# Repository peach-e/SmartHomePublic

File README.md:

# SmartHome System
Run your home from a Raspberry Pi! Specifically your gardening system and your ambient lights.

## Raspberry Pi Setup
### Notes
* The following steps are written for a Raspberry Pi 2 with a TP-Link Wifi Adapter (RTL8188EUS).
* My LAN router has been configured to recognise the MAC address of the Wi-Fi Adapter and associate it with the `__HOSTNAME_SERVER__` hostname and a fixed IP address.

### Steps
1. Download Raspbian Buster Lite and image it onto an SD Card.
2. Boot Up the Raspberry Pi. Log in with `pi`/`raspberry`.
3. Configure the RPi with `$ sudo raspi-config`:
    * Hostname:
        * Set to something memorable.
    * Password
        * Set to something else that isn't 'raspberry'.
    * Localization Options
        * Timezone: Set
        * Keyboard Layout: US, if you can figure out how to set it.
    * Network Options
        * Hostname: YOUR_HOSTNAME_GOES_HERE
    * Interfacing Options
        * SSH Server: Enable
4. Set Up RPi Wi-Fi to talk to my network.
    * Create a file called `/etc/network/interfaces.d/tplink` with the following lines:
        ```
        auto wlan0
        allow-hotplug wlan0
        iface wlan0 inet manual
        wpa-conf /etc/wpa_supplicant/wpa_supplicant.conf
        ```
    * Edit the file `/etc/wpa_supplicant/wpa_supplicant.conf` so that it reads as follows:
        ```
        ctrl_interface=DIR=/var/run/wpa_supplicant GROUP=netdev
        update_config=1
        country=US

        network={
            scan_ssid=1
            ssid="__WIFI_NETWORK_NAME__"
            psk="__WIFI_NETWORK_PASSWORD__"
        }
        ```
    * Reboot.
5. Install git with `$ sudo apt install git`.
6. Install the RF24 Module as described in the 'RF24 Setup' section.
7. Execute the 'Common Setup Steps'.
8. After running the setup script for the SmartHome project, have a look at the `dist.pth` file nested
   in the `virtualenv` directory and just sanity check that the files listed in there actually exist. If they don't, your RF24 libraries won't work unless you fix this:
    * look around in `/usr/local/lib/` for something related to `RF24<something something>.egg`.
    * update the `dist.pth` file and the setup script to point to the right library locations.
9. Power off the system. Connect any peripherals as required, and start the Pi.
10. Enable any mocks you will need, and practise running the server as root with
    ```
    /home/pi/SmartHome/scripts/start_system_in_background.sh
    ```
    Ensure that you can access the server and things work as expected.
11. If the Pi is intended for production use, modify your `/etc/rc.local` file by adding the following line before
   the exit command. This will enable the server and worker automatically on startup.
    ```
    /home/pi/SmartHome/scripts/start_system_in_background.sh
    ```
   (Double check that the path is correct, depending on where you cloned the repo).

## PC Setup
To get this going on your laptop, all you have to do is run the Common Setup steps. There may be an issue where 
you don't have the RPi python library installed. So just modify the `main.conf` file to enable the mockout. It's
also recommended that you have a solid IDE like Sublime Text ready to go to make some tidy code edits.

## Common Setup
### Dependencies
* Python 3.6+
* Pip3 (via the python3-pip package)
    * If you run `$ pip3 --version` you should see 3-point-something.

### Steps
1. Clone the repository.
    ```
    $ cd ~/Development
    $ git clone ssh://git@__HOSTNAME_LOCAL_GIT_SERVER__/home/git/SmartHome.git
    ```
2. Ensure your Python versions and PIP versions are set up.
3. Run the setup script
    ```
    $ ./scripts/setup_dev_environment.sh
    ```

## RF24 Setup
These steps are based on the Detailed Tutorial on Confluence "Tutorial - RPi + Arduino Hello World", which
were modified from the original steps at http://tmrh20.github.io/RF24/Python.html.

1. On the Raspberry Pi, enable SPI through `raspi-config`. Reboot.
2. Update your software (this might take a while)
    ```
    $ sudo apt update
    $ sudo apt upgrade
    ```
3. Install requisite software.
    ```
    $ sudo apt install python3-dev libboost-python-dev
    ```
4. Get the driver software on your Raspberry Pi.
    ```
    $ git clone https://github.com/nRF24/RF24.git
    ```
5. Change into the driver directory, build, and install the driver.
    ```
    $ cd RF24
    $ make
    $ sudo make install
6. Change into the pyRF24 library, install the setup tools dependency, and build the Python wrapper.
    ```
    $ cd pyRF24
    $ sudo apt install python3-setuptools
    $ python3 setup.py build
    $ sudo python3 setup.py install
    ```

## Normal Development
For use in a non-production environment. Before beginning, enable any mockouts in the `main.conf`
file if you think you need them.
1. After logging in, source the initialization script.
    ```
    $ source init_environment.sh
    ```
2. Change directory into the `app` directory and run the system.
    ```
    $ cd app
    $ ./run_system.py
    ```
Exit the application with Ctrl-C or run `$ killall python`.

## Re-Deployment
1. Deactivate any running systems with
    ```
    # killall python
    # killall python3
    # deactivate
    ```
2. Pull from master.
    ```
    $ git pull origin master
    ```
3. Run a git clean.
    ```
    $ git clean -dxf
    ```
4. Re-Deploy the repo.
    ```
    $ cd scripts
    $ ./setup_dev_environment.sh
    ```
5. Ideally, your default config file will already be set up for a production
   system. But, if you require a non-standard configuration, copy over another main.conf from the template
   and make any changes as necessary.
6. Reboot. Your changes should work.

## Hot Fix to Database
1. Deactivate any running systems with
    ```
    # killall python
    # killall python3
    # deactivate
    ```
2. Pull from master.
    ```
    $ git pull origin master
    ```
3. Update database by modifying `scripts/re_initialize_database.py`.
4. Delete the existing database
    ```
    $ rm db/system.db
    ```
5. Re-Deploy Database.
    ```
    $ . init_environment.sh
    $ ./scripts/re_initialize_database.py
    ```
6. Deactivate environment with `deactivate` and then start the system.
    ```
    $ sudo ./scripts/start_system_in_background.sh
    ```
7. Log out. Server should continue running.

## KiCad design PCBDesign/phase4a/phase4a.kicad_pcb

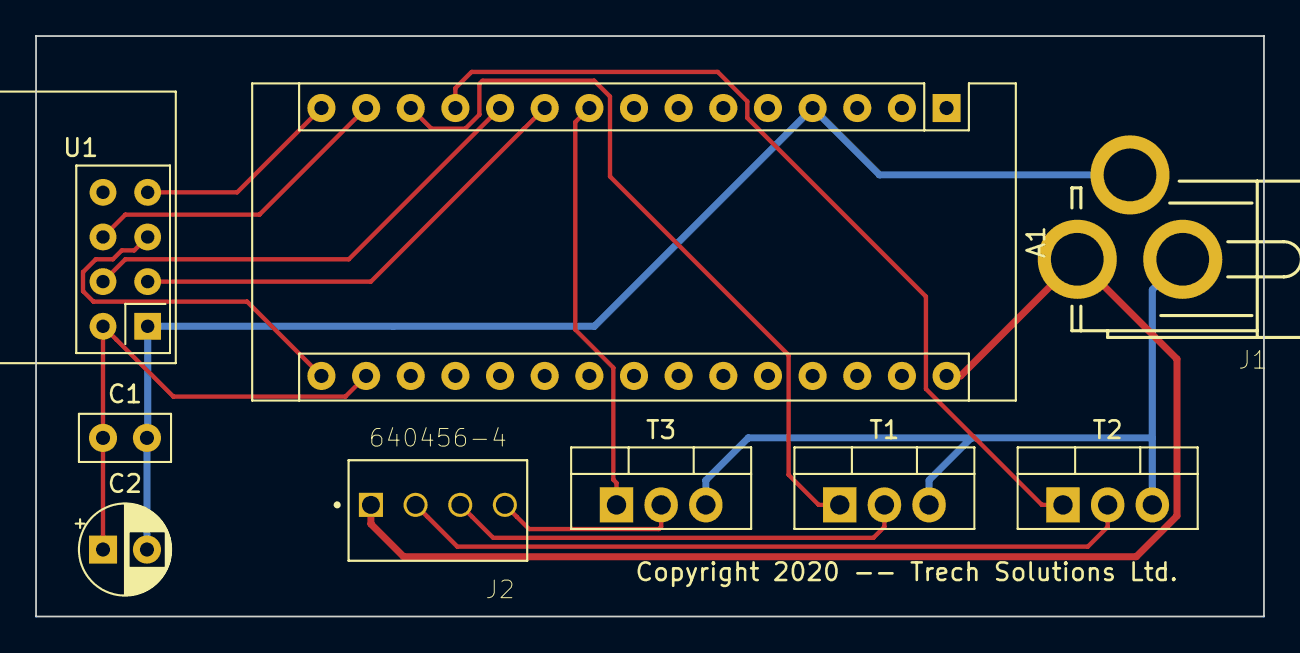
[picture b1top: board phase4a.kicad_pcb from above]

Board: 2 copper layers, 69.9 x 33.0 mm, 9 parts (0 on the bottom side), 14 nets.

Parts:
A1: Arduino_Nano_v2.x; Arduino_Nano
C1: 0.1u; C_Disc_D5.0mm_W2.5mm_P2.50mm
C2: 10u; CP_Radial_D5.0mm_P2.50mm
J1: PJ-002A
J2: 640456-4; TE_640456-4
T1, T2, T3: IRL2703PBF; TO-220-3_Vertical
U1: NRF24L01_Breakout; nRF24L01_Breakout

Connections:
/ARD_B: A1.9, T3.1
/ARD_CE: A1.10, U1.3
/ARD_CSN: A1.11, U1.4
/ARD_G: A1.12, T2.1
/ARD_MISO: A1.15, U1.7
/ARD_MOSI: A1.14, U1.6
/ARD_R: A1.13, T1.1
/ARD_RF24_VCC: A1.17, C1.1, C2.1, U1.2
/ARD_SCK: A1.16, U1.5
/CONN_B: J2.4, T3.2
/CONN_G: J2.2, T2.2
/CONN_R: J2.3, T1.2
GND: A1.4, C1.2, C2.2, J1.1, J1.2, T1.3, T2.3, T3.3, U1.1
VCC: A1.30, J1.3, J2.1

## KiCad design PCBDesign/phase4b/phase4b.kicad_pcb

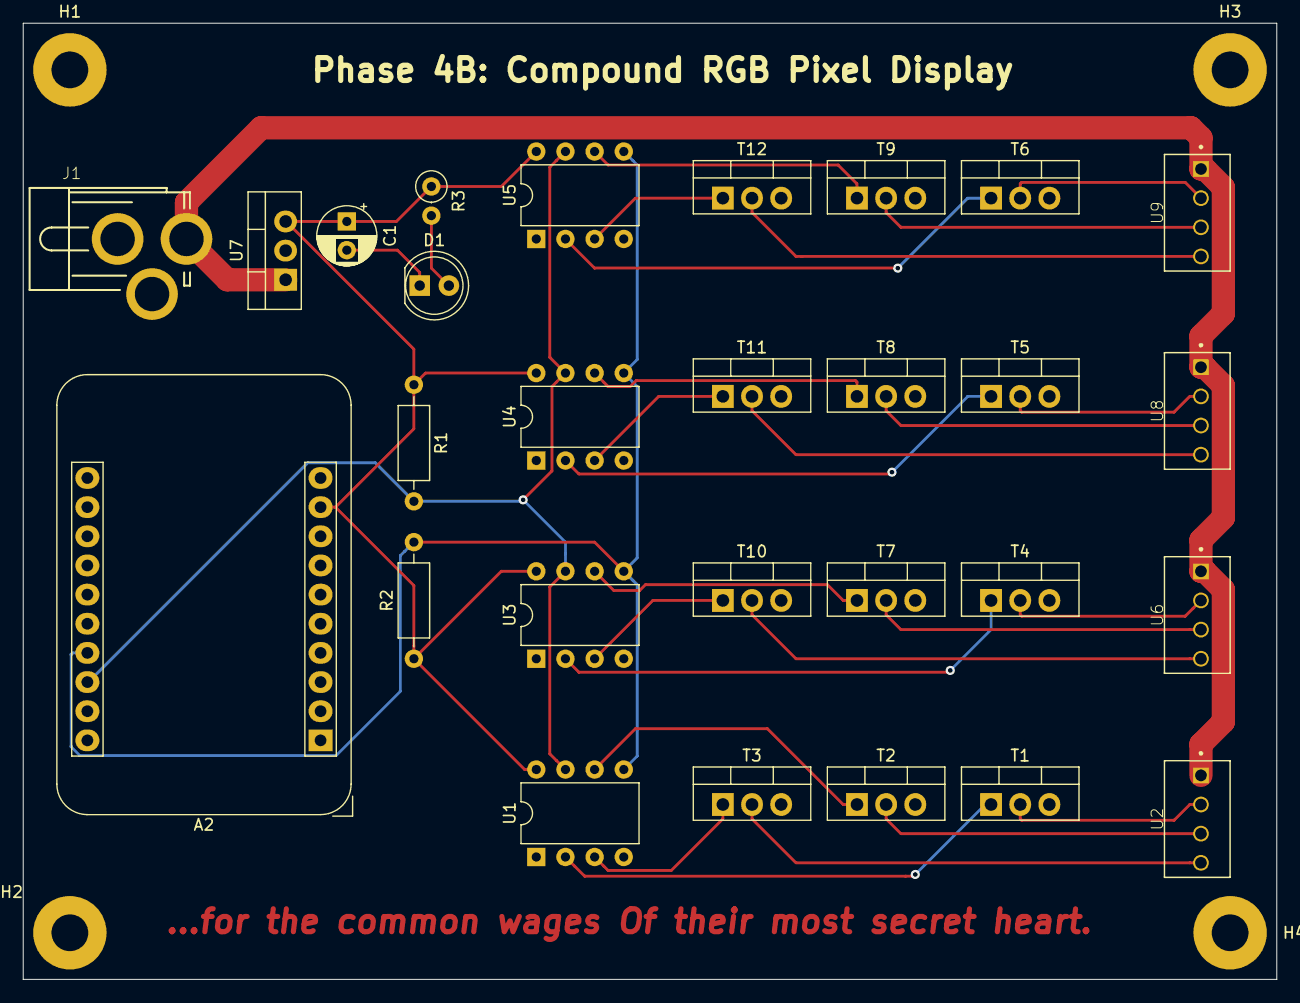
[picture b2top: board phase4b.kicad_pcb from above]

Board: 2 copper layers, 109.2 x 83.3 mm, 32 parts (0 on the bottom side), 30 nets.

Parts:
A2: Adafruit_HUZZAH_ESP8266_breakout
C1: 10uF; CP_Radial_D5.0mm_P2.50mm
D1: LED; LED_D5.0mm
H1, H2, H3, H4: MountingHole; MountingHole_3.2mm_M3_Pad
J1: PJ-002A
R1, R2: 1k; R_Axial_DIN0207_L6.3mm_D2.5mm_P10.16mm_Horizontal
R3: 10k; R_Axial_DIN0207_L6.3mm_D2.5mm_P2.54mm_Vertical
T1, T2, T3, T4, T5, T6, T7, T8, T9, T10, T11, T12: PSMN022-30PL; TO-220-3_Vertical
U1, U3, U4, U5: ATtiny85V-10PU; DIP-8_W7.62mm
U2, U6, U8, U9: RGB_LED_Strip; TE_640456-4
U7: MC7805CT-BP; TO-220-3_Vertical

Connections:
+12V: J1.3, U2.1, U6.1, U7.1, U8.1, U9.1
/SCL: A2.18, R1.2, U1.7, U3.7, U4.7, U5.7
/SDA: A2.17, R2.2, U1.5, U3.5, U4.5, U5.5
GND: A2.11, C1.2, D1.1, J1.1, J1.2, T1.3, T2.3, T3.3, T4.3, T5.3, T6.3, T7.3, T8.3, T9.3, T10.3, T11.3, T12.3, U1.4, U3.4, U4.4, U5.4, U7.2
unnamed: D1.2, R3.2
unnamed: T1.1, U1.2
unnamed: T1.2, U2.2
unnamed: T2.1, U1.6
unnamed: T2.2, U2.3
unnamed: T3.1, U1.3
unnamed: T3.2, U2.4
unnamed: T4.1, U3.2
unnamed: T4.2, U6.2
unnamed: T5.1, U4.2
unnamed: T5.2, U8.2
unnamed: T6.1, U5.2
unnamed: T6.2, U9.2
unnamed: T7.1, U3.6
unnamed: T7.2, U6.3
unnamed: T8.1, U4.6
unnamed: T8.2, U8.3
unnamed: T9.1, U5.6
unnamed: T9.2, U9.3
unnamed: T10.1, U3.3
unnamed: T10.2, U6.4
unnamed: T11.1, U4.3
unnamed: T11.2, U8.4
unnamed: T12.1, U5.3
unnamed: T12.2, U9.4
VCC: A2.9, C1.1, R1.1, R2.1, R3.1, U1.8, U3.8, U4.8, U5.8, U7.3

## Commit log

2020-06-02 Start with the gitignore
2020-06-02 Initial release
2020-10-09 Introduce changes from Phase 5: A re-hashed database, new peripherals, cleaned up mocks, and some bug fixes on server.

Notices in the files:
PCBDesign/phase4a/phase4a.kicad_pcb:
Copyright 2020 -- Trech Solutions Ltd.
